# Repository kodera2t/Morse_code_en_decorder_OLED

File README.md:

# Morse_code_en_decorder_OLED
Morse code en decorder based on Arduino with OLED SPI display. Word per minutes is adjustable by rotary-encorder.
As a by-product project to my Tiny computer project, I made an stand-alone Tiny Morse code encoder/decorder. 
The procedure to make and program is almost same as previous one, 
http://hackaday.io/project/4201-really-tiny-computer-for-basic-bitlash-and-morse 
but the hardware is not same any more.

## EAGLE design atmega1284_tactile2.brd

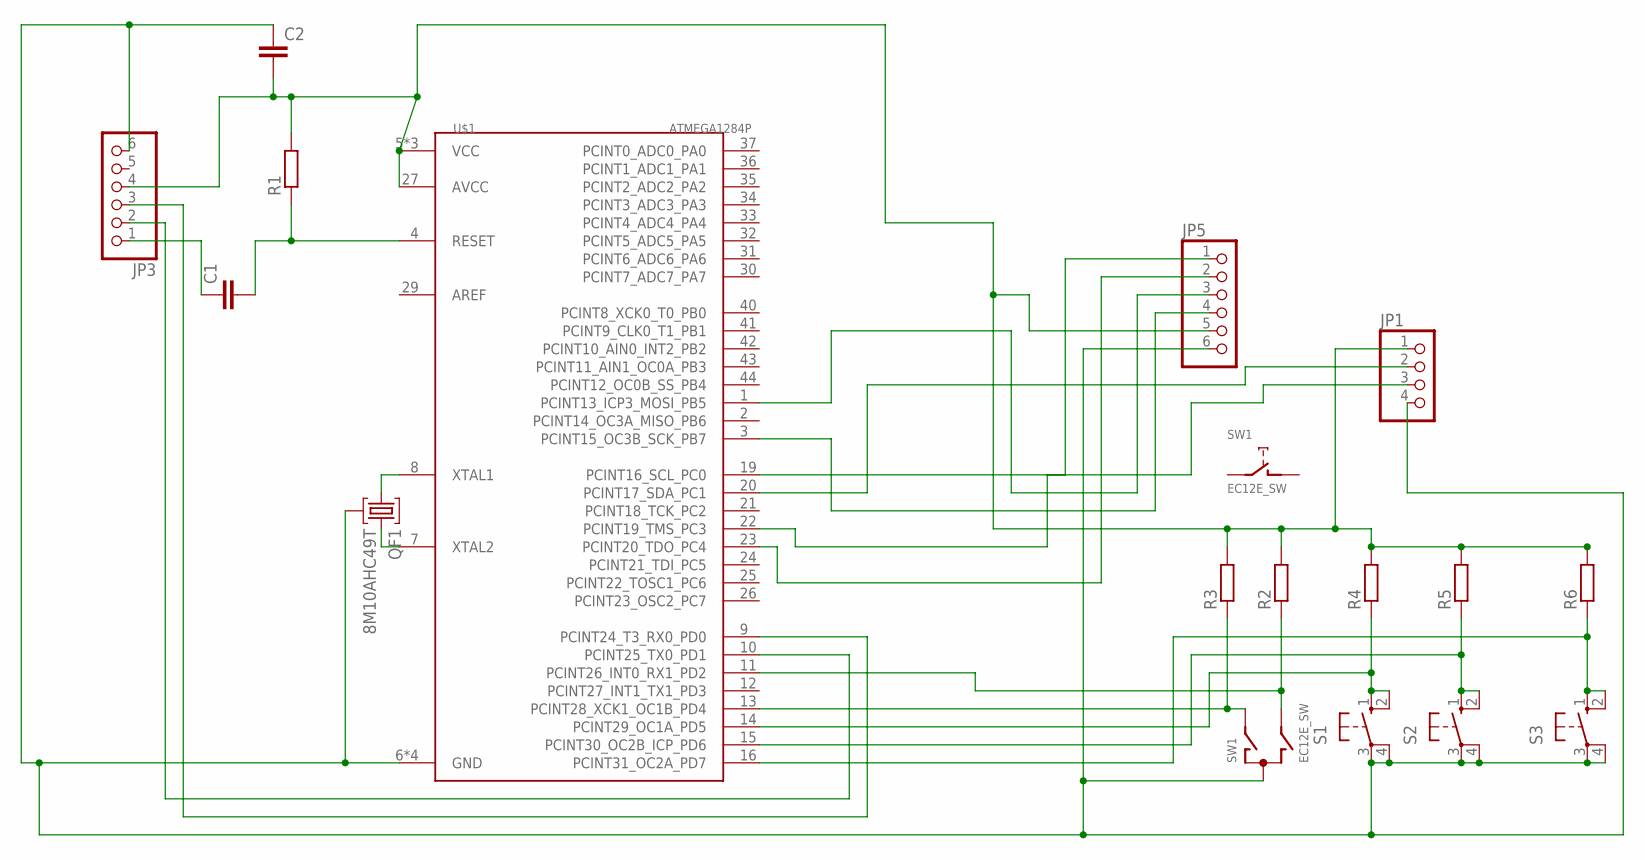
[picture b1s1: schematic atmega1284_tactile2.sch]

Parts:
C1, C2: C-EUC0805; C0805
JP1: PINHD-1X4; 1X04
JP3, JP5: PINHD-1X6; 1X06
QF1: 8M10AHC49T; HC49U
R1, R2, R3, R4, R5, R6: R-EU_R0805; R0805
S1, S2, S3: 10-XX; B3F-10XX
SW1: EC12E_SW; ALPS_EC12E_SW
U$1: ATMEGA1284P; TQFP44

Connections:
unnamed: JP5.3, U$1.1 (PCINT13_ICP3_MOSI_PB5)
unnamed: QF1.1, U$1.8 (XTAL1)
unnamed: QF1.3, U$1.7 (XTAL2)
unnamed: C2.1, JP1.4, JP3.6, JP5.6, QF1.2, S1.3, S1.4 (P1), S2.3, S2.4 (P1), S3.3, S3.4 (P1), SW1.C, U$1.6 (GND), U$1.18 (GND), U$1.28 (GND), U$1.39 (GND)
unnamed: JP5.4, U$1.3 (PCINT15_OC3B_SCK_PB7)
unnamed: R2.1, SW1.B, U$1.11 (PCINT26_INT0_RX1_PD2)
unnamed: C1.2, R1.1, U$1.4 (RESET)
unnamed: C1.1, JP3.1
unnamed: JP3.2, U$1.10 (PCINT25_TX0_PD1)
unnamed: JP3.3, U$1.9 (PCINT24_T3_RX0_PD0)
unnamed: JP5.1, U$1.22 (PCINT19_TMS_PC3)
unnamed: JP5.2, U$1.23 (PCINT20_TDO_PC4)
unnamed: R3.1, SW1.A, U$1.13 (PCINT28_XCK1_OC1B_PD4)
unnamed: R4.1, S1.1 (S), S1.2 (S1), U$1.14 (PCINT29_OC1A_PD5)
unnamed: R5.1, S2.1 (S), S2.2 (S1), U$1.15 (PCINT30_OC2B_ICP_PD6)
unnamed: R6.1, S3.1 (S), S3.2 (S1), U$1.16 (PCINT31_OC2A_PD7)
unnamed: C2.2, JP1.1, JP3.4, JP5.5, R1.2, R2.2, R3.2, R4.2, R5.2, R6.2, U$1.5 (VCC), U$1.17 (VCC), U$1.27 (AVCC), U$1.38 (VCC)
unnamed: JP1.2, U$1.20 (PCINT17_SDA_PC1)
unnamed: JP1.3, U$1.19 (PCINT16_SCL_PC0)

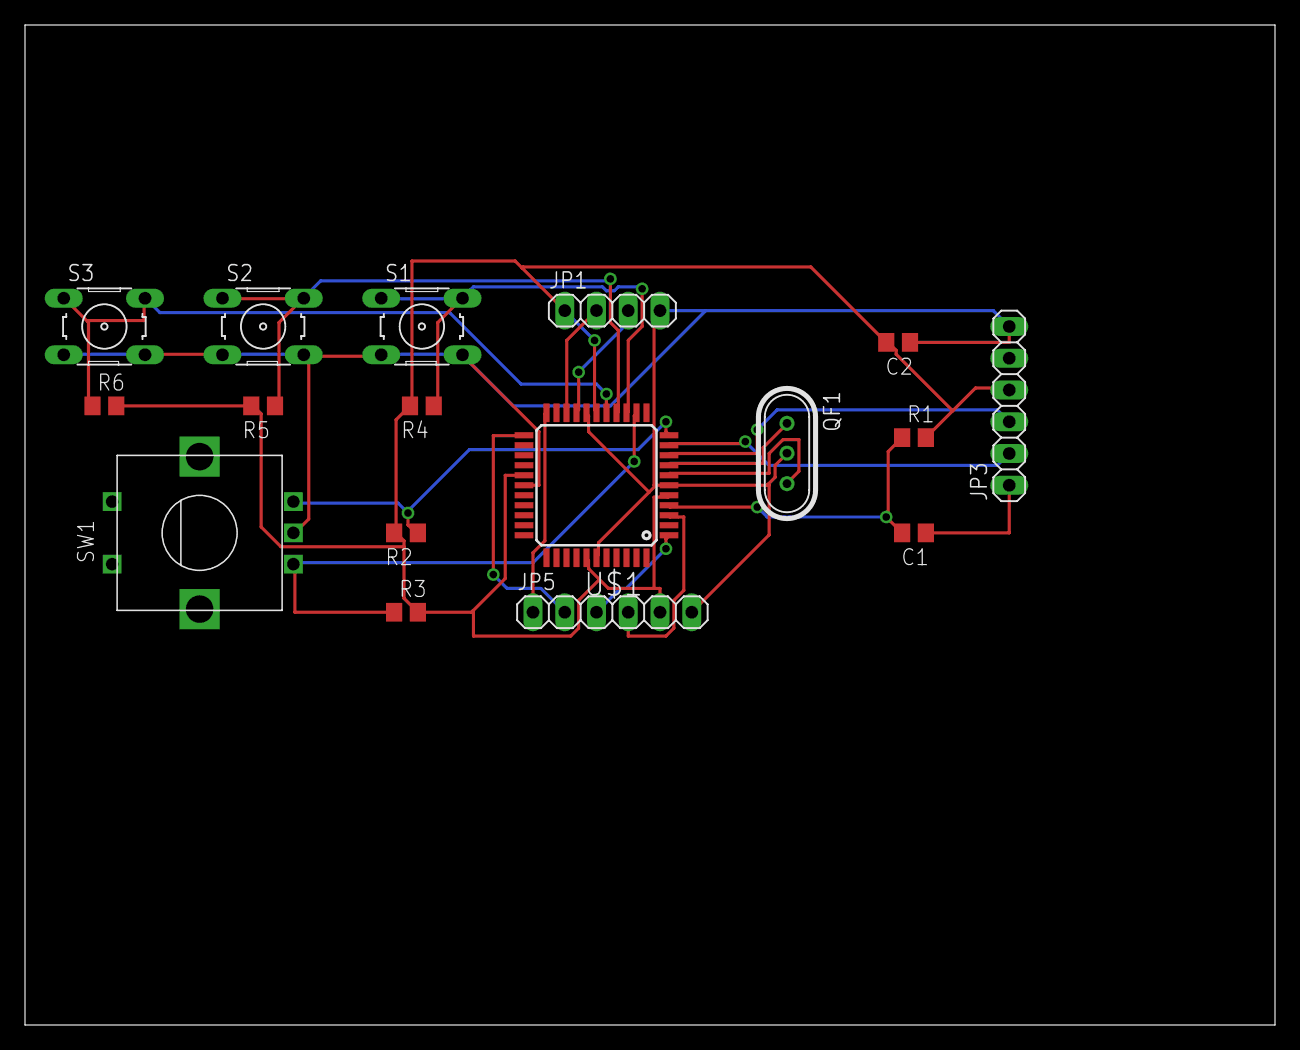
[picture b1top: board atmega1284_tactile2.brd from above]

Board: 2 copper layers, 100.0 x 80.0 mm, 17 parts (0 on the bottom side), 19 nets.

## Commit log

2015-02-11 initial submission
    initial submission!
